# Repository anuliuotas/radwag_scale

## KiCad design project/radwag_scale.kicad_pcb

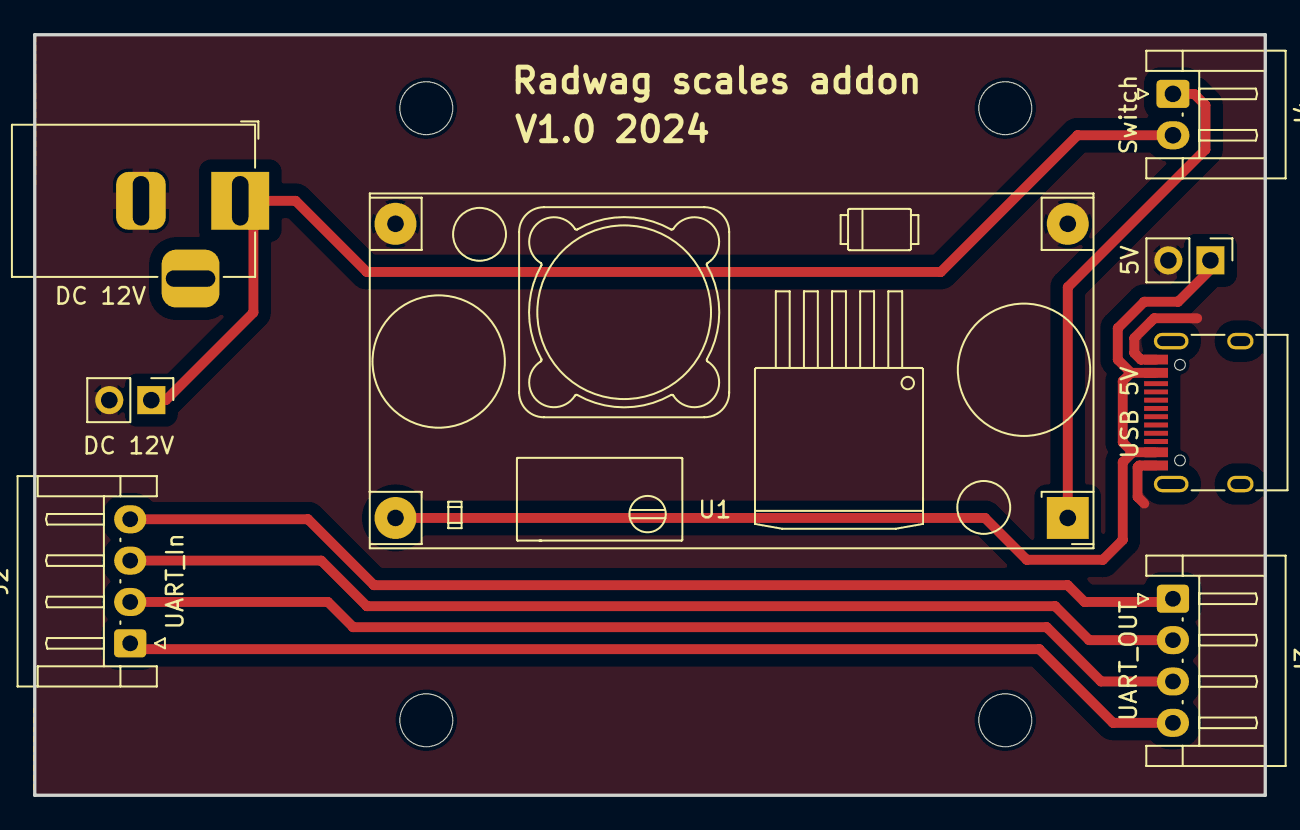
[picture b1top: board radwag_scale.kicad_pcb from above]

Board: 2 copper layers, 74.4 x 46.0 mm, 12 parts (0 on the bottom side), 8 nets.

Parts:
DC 12V: Barrel_Jack_MountingPin; BarrelJack_Horizontal
DC 12V#2: Power IN; PinHeader_1x02_P2.54mm_Vertical
H1, H2, H3, H4: MountingHole; MountingHole_3.2mm_M3
J2: UART_In; JST_EH_S4B-EH_1x04_P2.50mm_Horizontal
J3: UART_OUT; JST_EH_S4B-EH_1x04_P2.50mm_Horizontal
J4: Switch; JST_EH_S2B-EH_1x02_P2.50mm_Horizontal
J5: 5V; PinHeader_1x02_P2.54mm_Vertical
U1: YAAJ_DCDC_StepDown_LM2596
USB 5V: TYPE-C-31-M-12; USB_C_Receptacle_HRO_TYPE-C-31-M-12

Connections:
+5V: J5.1, U1.4 (Vout), USB 5V.A4 (VBUS), USB 5V.A9 (VBUS), USB 5V.B4 (VBUS), USB 5V.B9 (VBUS)
+12V: DC 12V.1, DC 12V#2.1, J4.2
/+12V_SW: J4.1, U1.1 (Vin)
/UART_1: J2.1, J3.4
/UART_2: J2.2, J3.3
/UART_3: J2.3, J3.2
/UART_4: J2.4, J3.1
GND: DC 12V.2, DC 12V#2.2, J5.2, U1.2 (GND), U1.3 (GND), USB 5V.A1 (GND), USB 5V.A12 (GND), USB 5V.B1 (GND), USB 5V.B12 (GND)

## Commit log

2024-05-26 v1 cads
2024-06-03 added pull mode
2024-06-03 git ignore update
